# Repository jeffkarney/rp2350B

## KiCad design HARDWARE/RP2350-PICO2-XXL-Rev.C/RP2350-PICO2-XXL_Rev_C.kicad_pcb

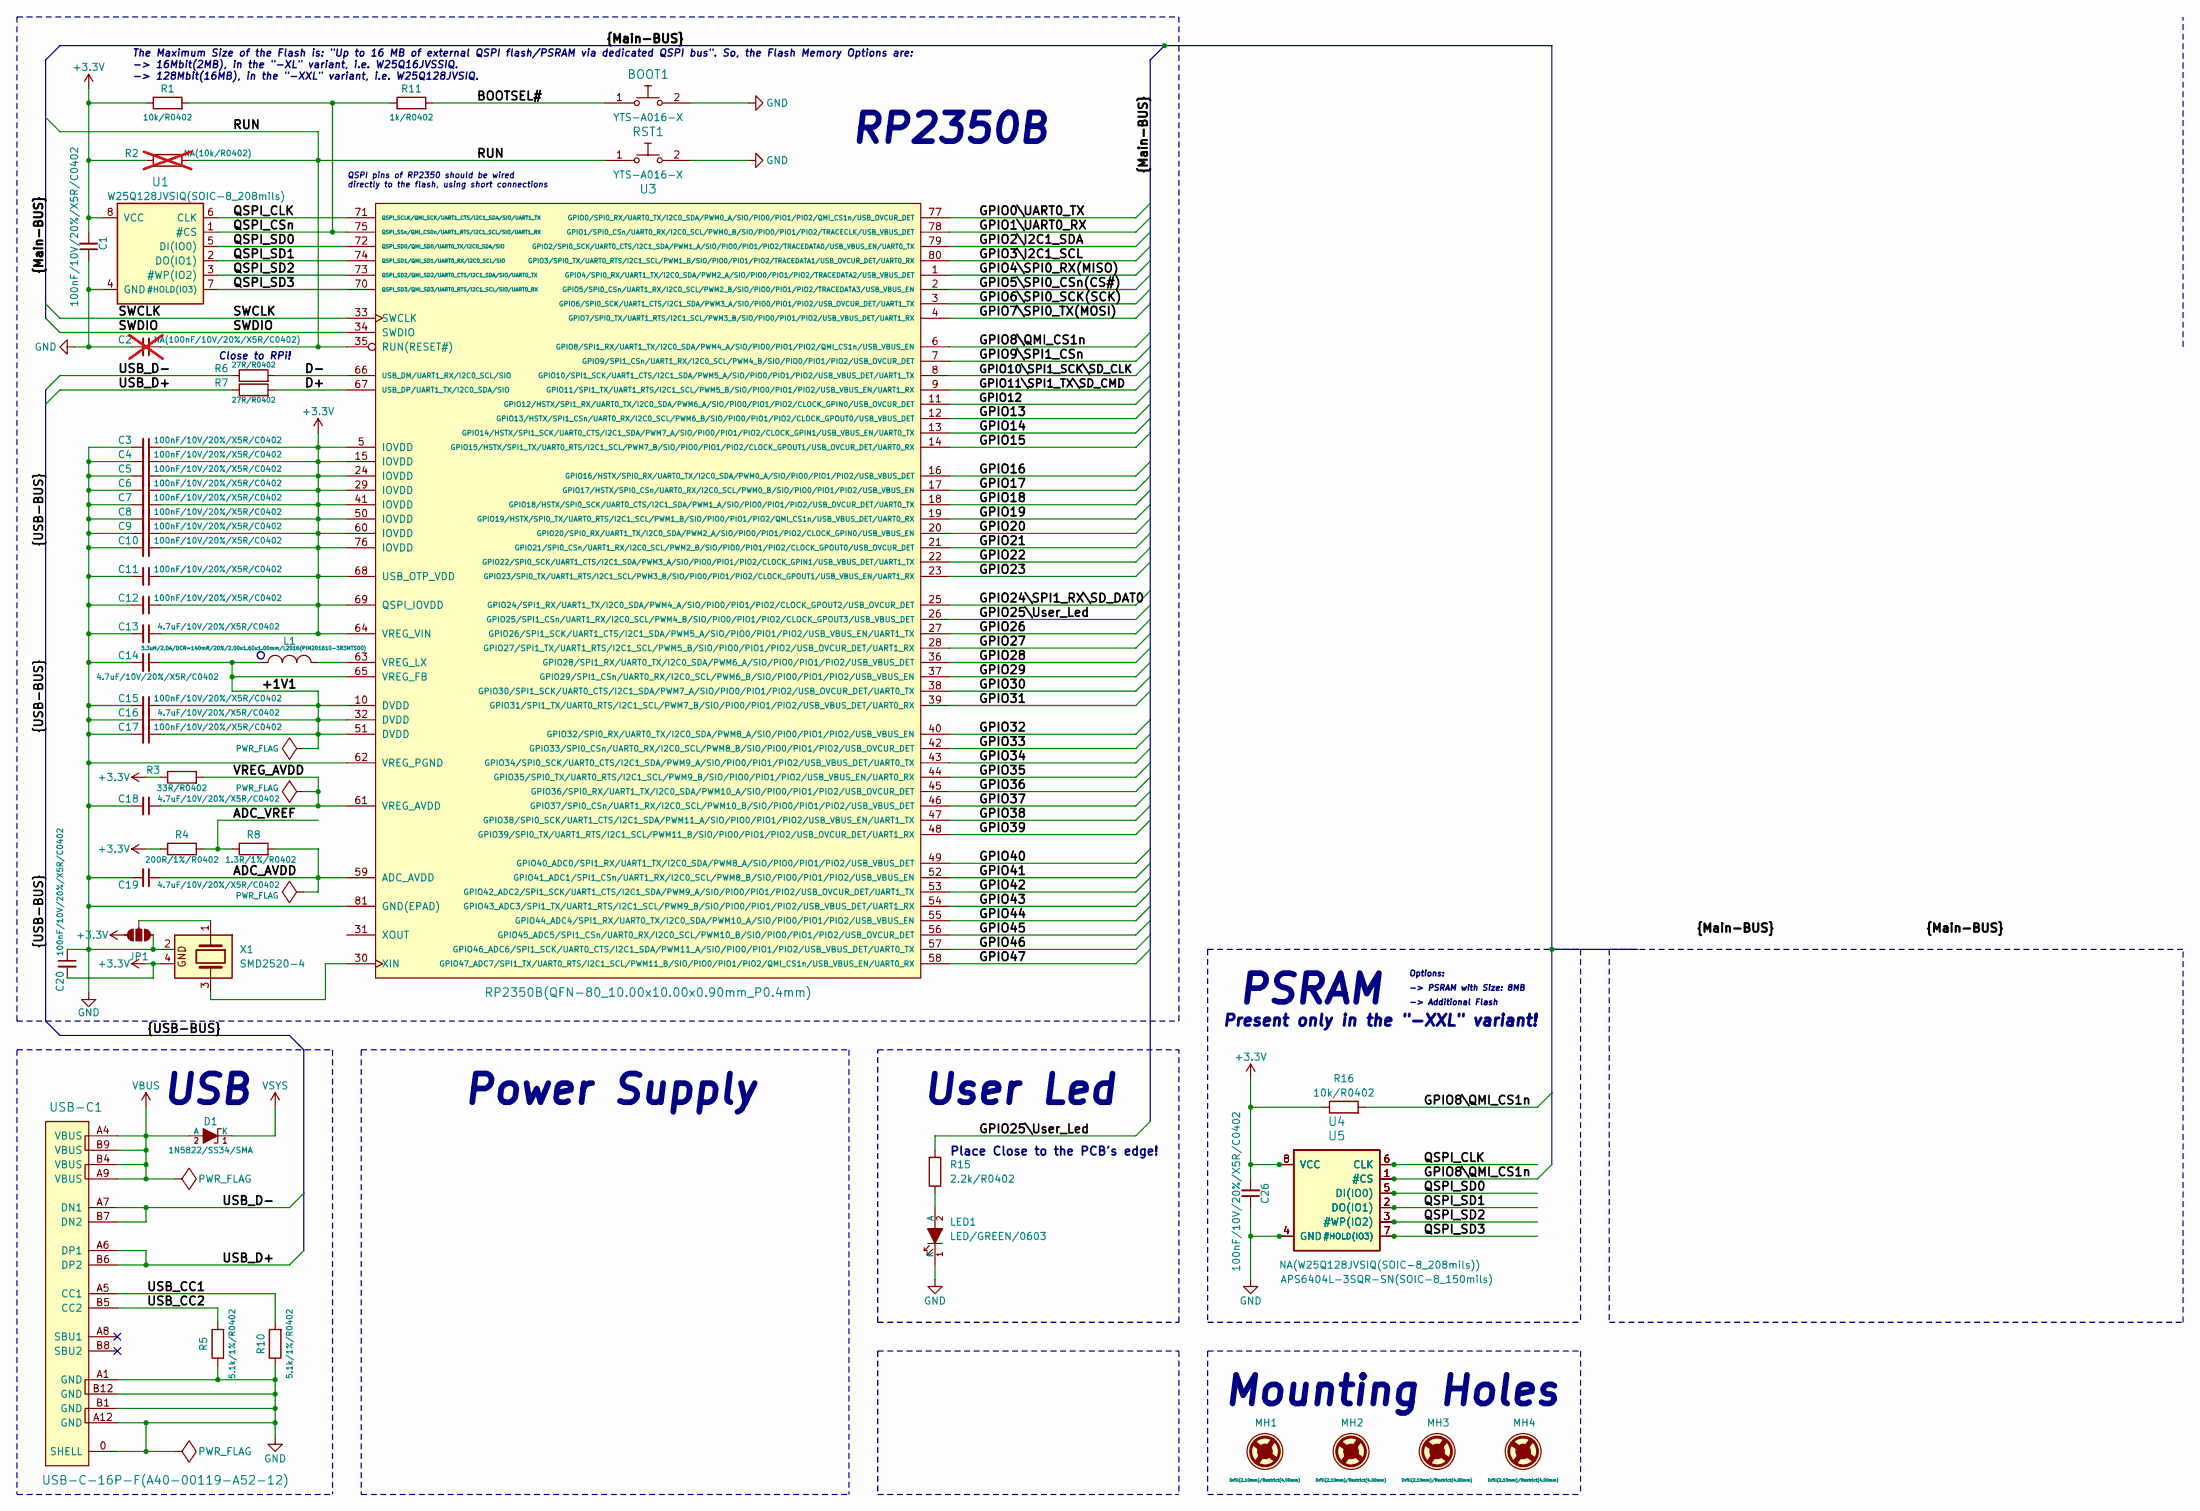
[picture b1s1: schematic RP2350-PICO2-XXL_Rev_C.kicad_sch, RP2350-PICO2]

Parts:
BOOT1: YTS-A016-X
C1, C3, C4, C5, C6, C7, C8, C9, C10, C11, C12, C15, C17, C20, C26: 100nF/10V/20%/X5R/C0402; C_0402_5MIL_DWS
C2: NA(100nF/10V/20%/X5R/C0402); C_0402_5MIL_DWS; not fitted
C13, C14, C16, C18, C19: 4.7uF/10V/20%/X5R/C0402; C_0402_5MIL_DWS
D1: 1N5822/SS34/SMA; SMA-KA
JP1: Jumper_3_NO_NoSilk
L1: 3.3uH/2.0A/DCR=140mR/20%/2.00x1.60x1.00mm/L2016(P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; L_2016_MM
LED1: LED/GREEN/0603; LED_0603_KA
MH1, MH2, MH3, MH4: Drill(2.10mm)/Restrict(4.00mm); Mounting_Hole_Drill-2.1mm_Clerance-4mm
R1, R16: 10k/R0402; R_0402_5MIL_DWS
R2: NA(10k/R0402); R_0402_5MIL_DWS; not fitted
R3: 33R/R0402; R_0402_5MIL_DWS
R4: 200R/1%/R0402; R_0402_5MIL_DWS
R5, R10: 5.1k/1%/R0402; R_0402_5MIL_DWS
R6, R7: 27R/R0402; R_0402_5MIL_DWS
R8: 1.3R/1%/R0402; R_0402_5MIL_DWS
R11: 1k/R0402; R_0402_5MIL_DWS
R15: 2.2k/R0402; R_0402_5MIL_DWS
RST1: YTS-A016-X
U1: W25Q128JVSIQ(SOIC-8_208mils); SO-8_208mil
U3: RP2350B(QFN-80_10.00x10.00x0.90mm_P0.4mm); QFN-80_10.00x10.00x0.90mm_P0.4mm
U4: NA(W25Q128JVSIQ(SOIC-8_208mils)); SO-8_208mil
U5: APS6404L-3SQR-SN(SOIC-8_150mils); SO-8
USB-C1: USB-C-16P-F(A40-00119-A52-12); USB2.0_TYPE-C(A40-00119-A52-12)_Paste
X1: SMD2520-4; Crystal_SMD_2520-4Pin_2.5x2.0mm

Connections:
+3.3V: C1.2, C3.1, C4.1, C5.1, C6.1, C7.1, C8.1, C9.1, C10.1, C11.1, C12.1, C13.1, C20.2, C26.2, JP1.3 (C), R1.1, R2.1, R3.1, R4.1, R16.1, U1.8 (VCC), U3.5 (IOVDD), U3.15 (IOVDD), U3.24 (IOVDD), U3.29 (IOVDD), U3.41 (IOVDD), U3.50 (IOVDD), U3.60 (IOVDD), U3.64 (VREG_VIN), U3.68 (USB_OTP_VDD), U3.69 (QSPI_IOVDD), U3.76 (IOVDD), U4.8 (VCC), U5.8 (VCC), X1.4
/+1V1: C14.1, C15.1, C16.1, C17.1, L1.1, U3.10 (DVDD), U3.32 (DVDD), U3.51 (DVDD), U3.65 (VREG_FB)
/ADC_AVDD: C19.1, R8.2, U3.59 (ADC_AVDD)
/ADC_VREF: R4.2, R8.1
/BOOTSEL#: BOOT1.1, R11.2
/D+: R7.2, U3.67 (USB_DP/UART1_TX/I2C0_SDA/SIO)
/D-: R6.2, U3.66 (USB_DM/UART1_RX/I2C0_SCL/SIO)
/GPIO0\UART0_TX: U3.77 (GPIO0/SPI0_RX/UART0_TX/I2C0_SDA/PWM0_A/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)
/GPIO1\UART0_RX: U3.78 (GPIO1/SPI0_CSn/UART0_RX/I2C0_SCL/PWM0_B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)
/GPIO2\I2C1_SDA: U3.79 (GPIO2/SPI0_SCK/UART0_CTS/I2C1_SDA/PWM1_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)
/GPIO3\I2C1_SCL: U3.80 (GPIO3/SPI0_TX/UART0_RTS/I2C1_SCL/PWM1_B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)
/GPIO4\SPI0_RX(MISO): U3.1 (GPIO4/SPI0_RX/UART1_TX/I2C0_SDA/PWM2_A/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)
/GPIO5\SPI0_CSn(CS#): U3.2 (GPIO5/SPI0_CSn/UART1_RX/I2C0_SCL/PWM2_B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)
/GPIO6\SPI0_SCK(SCK): U3.3 (GPIO6/SPI0_SCK/UART1_CTS/I2C1_SDA/PWM3_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)
/GPIO7\SPI0_TX(MOSI): U3.4 (GPIO7/SPI0_TX/UART1_RTS/I2C1_SCL/PWM3_B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)
/GPIO8\QMI_CS1n: R16.2, U3.6 (GPIO8/SPI1_RX/UART1_TX/I2C0_SDA/PWM4_A/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), U4.1 (#CS), U5.1 (#CS)
/GPIO9\SPI1_CSn: U3.7 (GPIO9/SPI1_CSn/UART1_RX/I2C0_SCL/PWM4_B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)
/GPIO10\SPI1_SCK\SD_CLK: U3.8 (GPIO10/SPI1_SCK/UART1_CTS/I2C1_SDA/PWM5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)
/GPIO11\SPI1_TX\SD_CMD: U3.9 (GPIO11/SPI1_TX/UART1_RTS/I2C1_SCL/PWM5_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)
/GPIO12: U3.11 (GPIO12/HSTX/SPI1_RX/UART0_TX/I2C0_SDA/P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)
/GPIO13: U3.12 (GPIO13/HSTX/SPI1_CSn/UART0_RX/I2C0_SCL/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)
/GPIO14: U3.13 (GPIO14/HSTX/SPI1_SCK/UART0_CTS/I2C1_SDA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)
/GPIO15: U3.14 (GPIO15/HSTX/SPI1_TX/UART0_RTS/I2C1_SCL/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)
/GPIO16: U3.16 (GPIO16/HSTX/SPI0_RX/UART0_TX/I2C0_SDA/P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)
/GPIO17: U3.17 (GPIO17/HSTX/SPI0_CSn/UART0_RX/I2C0_SCL/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)
/GPIO18: U3.18 (GPIO18/HSTX/SPI0_SCK/UART0_CTS/I2C1_SDA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)
/GPIO19: U3.19 (GPIO19/HSTX/SPI0_TX/UART0_RTS/I2C1_SCL/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)
/GPIO20: U3.20 (GPIO20/SPI0_RX/UART1_TX/I2C0_SDA/PWM2_A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)
/GPIO21: U3.21 (GPIO21/SPI0_CSn/UART1_RX/I2C0_SCL/PWM2_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)
/GPIO22: U3.22 (GPIO22/SPI0_SCK/UART1_CTS/I2C1_SDA/PWM3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)
/GPIO23: U3.23 (GPIO23/SPI0_TX/UART1_RTS/I2C1_SCL/PWM3_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)
/GPIO24\SPI1_RX\SD_DAT0: U3.25 (GPIO24/SPI1_RX/UART1_TX/I2C0_SDA/PWM4_A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)
/GPIO25\User_Led: R15.2, U3.26 (GPIO25/SPI1_CSn/UART1_RX/I2C0_SCL/PWM4_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)
/GPIO26: U3.27 (GPIO26/SPI1_SCK/UART1_CTS/I2C1_SDA/PWM5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)
/GPIO27: U3.28 (GPIO27/SPI1_TX/UART1_RTS/I2C1_SCL/PWM5_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)
/GPIO28: U3.36 (GPIO28/SPI1_RX/UART0_TX/I2C0_SDA/PWM6_A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)
/GPIO29: U3.37 (GPIO29/SPI1_CSn/UART0_RX/I2C0_SCL/PWM6_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)
/GPIO30: U3.38 (GPIO30/SPI1_SCK/UART0_CTS/I2C1_SDA/PWM7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)
/GPIO31: U3.39 (GPIO31/SPI1_TX/UART0_RTS/I2C1_SCL/PWM7_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)
/GPIO32: U3.40 (GPIO32/SPI0_RX/UART0_TX/I2C0_SDA/PWM8_A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)
/GPIO33: U3.42 (GPIO33/SPI0_CSn/UART0_RX/I2C0_SCL/PWM8_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)
/GPIO34: U3.43 (GPIO34/SPI0_SCK/UART0_CTS/I2C1_SDA/PWM9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)
/GPIO35: U3.44 (GPIO35/SPI0_TX/UART0_RTS/I2C1_SCL/PWM9_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)
/GPIO36: U3.45 (GPIO36/SPI0_RX/UART1_TX/I2C0_SDA/PWM10_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)
/GPIO37: U3.46 (GPIO37/SPI0_CSn/UART1_RX/I2C0_SCL/PWM10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)
/GPIO38: U3.47 (GPIO38/SPI0_SCK/UART1_CTS/I2C1_SDA/PWM1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)
/GPIO39: U3.48 (GPIO39/SPI0_TX/UART1_RTS/I2C1_SCL/PWM11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)
/GPIO40: U3.49 (GPIO40_ADC0/SPI1_RX/UART1_TX/I2C0_SDA/P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)
/GPIO41: U3.52 (GPIO41_ADC1/SPI1_CSn/UART1_RX/I2C0_SCL/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)
/GPIO42: U3.53 (GPIO42_ADC2/SPI1_SCK/UART1_CTS/I2C1_SDA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)
/GPIO43: U3.54 (GPIO43_ADC3/SPI1_TX/UART1_RTS/I2C1_SCL/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)
/GPIO44: U3.55 (GPIO44_ADC4/SPI1_RX/UART0_TX/I2C0_SDA/P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)
/GPIO45: U3.56 (GPIO45_ADC5/SPI1_CSn/UART0_RX/I2C0_SCL/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)
/GPIO46: U3.57 (GPIO46_ADC6/SPI1_SCK/UART0_CTS/I2C1_SDA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)
/GPIO47: U3.58 (GPIO47_ADC7/SPI1_TX/UART0_RTS/I2C1_SCL/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)
/QSPI_CLK: U1.6 (CLK), U3.71 (QSPI_SCLK/QMI_SCK/UART1_CTS/I2C1_SDA/SI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), U4.6 (CLK), U5.6 (CLK)
/QSPI_CSn: R1.2, R11.1, U1.1 (#CS), U3.75 (QSPI_SSn/QMI_CS0n/UART1_RTS/I2C1_SCL/SI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)
/QSPI_SD0: U1.5 (DI(IO0)), U3.72 (QSPI_SD0/QMI_SD0/UART0_TX/I2C0_SDA/SIO), U4.5 (DI(IO0)), U5.5 (DI(IO0))
/QSPI_SD1: U1.2 (DO(IO1)), U3.74 (QSPI_SD1/QMI_SD1/UART0_RX/I2C0_SCL/SIO), U4.2 (DO(IO1)), U5.2 (DO(IO1))
/QSPI_SD2: U1.3 (#WP(IO2)), U3.73 (QSPI_SD2/QMI_SD2/UART0_CTS/I2C1_SDA/SIO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), U4.3 (#WP(IO2)), U5.3 (#WP(IO2))
/QSPI_SD3: U1.7 (#HOLD(IO3)), U3.70 (QSPI_SD3/QMI_SD3/UART0_RTS/I2C1_SCL/SIO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), U4.7 (#HOLD(IO3)), U5.7 (#HOLD(IO3))
/RUN: C2.1, R2.2, RST1.1, U3.35 (RUN(RESET#))
/SWCLK: U3.33 (SWCLK)
/SWDIO: U3.34 (SWDIO)
/USB_CC1: R10.2, USB-C1.A5 (CC1)
/USB_CC2: R5.2, USB-C1.B5 (CC2)
/USB_D+: R7.1, USB-C1.A6 (DP1), USB-C1.B6 (DP2)
/USB_D-: R6.1, USB-C1.A7 (DN1), USB-C1.B7 (DN2)
/VREG_AVDD: C18.1, R3.2, U3.61 (VREG_AVDD)
GND: BOOT1.2, C1.1, C2.2, C3.2, C4.2, C5.2, C6.2, C7.2, C8.2, C9.2, C10.2, C11.2, C12.2, C13.2, C14.2, C15.2, C16.2, C17.2, C18.2, C19.2, C20.1, C26.1, JP1.1 (A), LED1.1 (K), R5.1, R10.1, RST1.2, U1.4 (GND), U3.62 (VREG_PGND), U3.81 (GND(EPAD)), U4.4 (GND), U5.4 (GND), USB-C1.0 (SHELL), USB-C1.A1 (GND), USB-C1.A12 (GND), USB-C1.B1 (GND), USB-C1.B12 (GND), X1.2
unnamed: JP1.2 (B), X1.1
unnamed: LED1.2 (A), R15.1
unnamed: L1.2, U3.63 (VREG_LX)
unnamed: U3.30 (XIN), X1.3
VBUS: D1.2 (A), USB-C1.A4 (VBUS), USB-C1.A9 (VBUS), USB-C1.B4 (VBUS), USB-C1.B9 (VBUS)
VSYS: D1.1 (K)

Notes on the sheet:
Present only in the "-XXL" variant!
QSPI pins of RP2350 should be wired directly to the flash, using short connections
-> PSRAM with Size: 8MB
The Maximum Size of the Flash is: "Up to 16 MB of external QSPI flash/PSRAM via dedicated QSPI bus". So, the Flash Memory Options are: -> 16Mbit(2MB), in the "-XL" variant, i.e. W25Q16JVSSIQ. -> 128Mbit(16MB), in the "-XXL" variant, i.e. W25Q128JVSIQ.
USB
User Led
Options:
-> Additional Flash
Place Close to the PCB's edge!
Close to RPi!
RP2350B
Mounting Holes
Power Supply
PSRAM

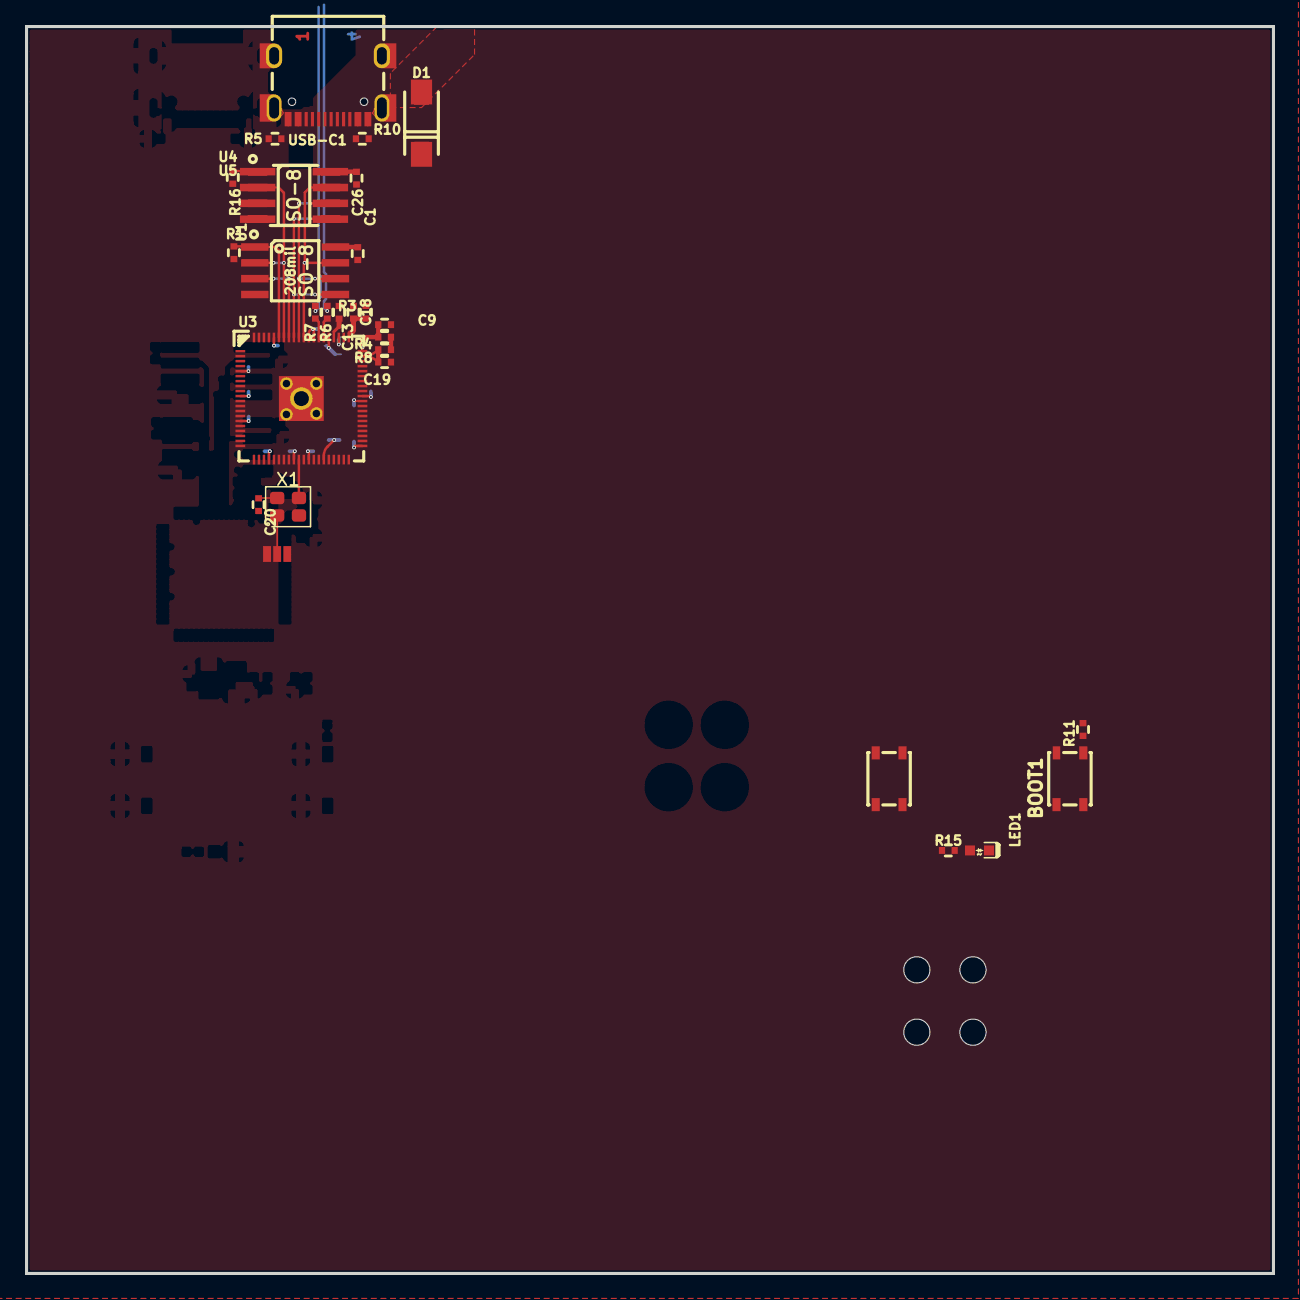
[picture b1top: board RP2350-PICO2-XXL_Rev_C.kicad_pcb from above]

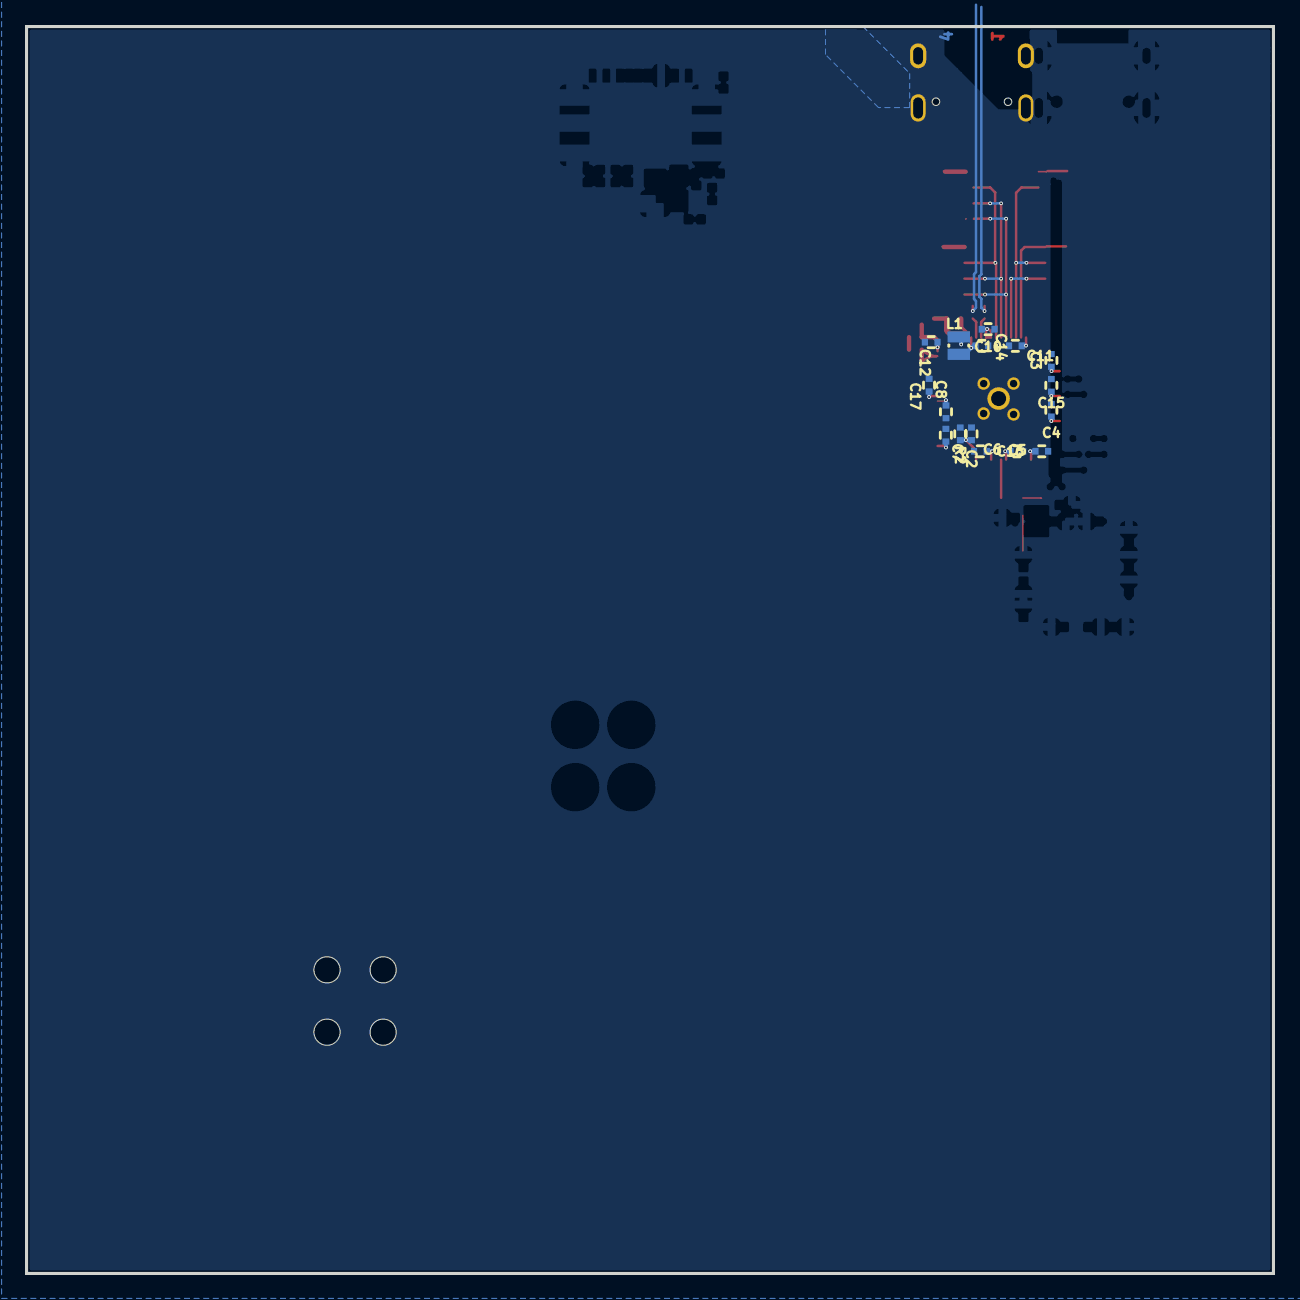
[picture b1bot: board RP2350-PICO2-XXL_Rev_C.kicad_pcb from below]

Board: 4 copper layers, 100.0 x 100.0 mm, 49 parts (16 on the bottom side), 27 nets.

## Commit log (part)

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2025-11-11 Update
    Added dimensions
